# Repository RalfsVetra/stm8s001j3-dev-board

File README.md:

# STM8S001J3 development board

A simple and easy to use development board for STM8S001J3 microcontroller. This is a part of my larger project where I explore hardware and firmware.

## License
This project is licensed under the MIT License - see the [LICENSE](/LICENSE) file for details.

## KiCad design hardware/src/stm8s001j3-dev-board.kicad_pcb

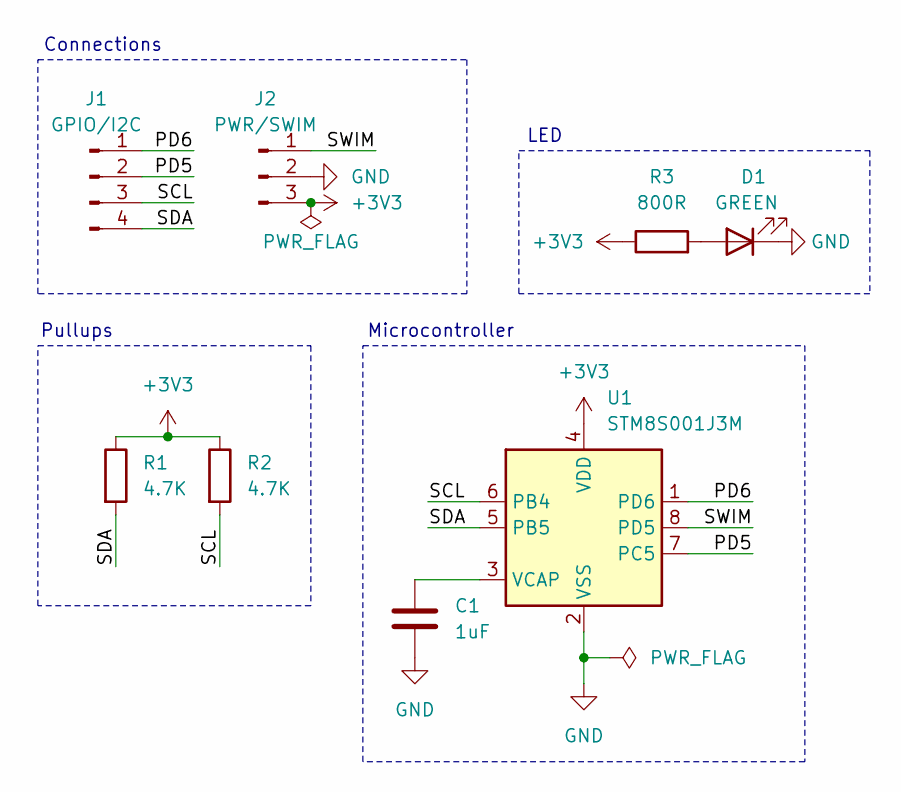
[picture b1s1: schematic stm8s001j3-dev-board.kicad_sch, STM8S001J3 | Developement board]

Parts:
C1: 1uF; C_0603_1608Metric
D1: GREEN; LED_0603_1608Metric
J1: GPIO/I2C; PinHeader_1x04_P2.54mm_Vertical
J2: PWR/SWIM; PinHeader_1x03_P2.54mm_Vertical
R1, R2: 4.7K; R_0603_1608Metric
R3: 800R; R_0603_1608Metric
U1: STM8S001J3M; SO-8_3.9x4.9mm_P1.27mm

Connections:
+3V3: J2.3, R1.1, R2.1, R3.1, U1.4 (VDD)
/PD5: J1.2, U1.7 (PC5)
/PD6: J1.1, U1.1 (PD6)
/SCL: J1.3, R2.2, U1.6 (PB4)
/SDA: J1.4, R1.2, U1.5 (PB5)
/SWIM: J2.1, U1.8 (PD5)
GND: C1.2, D1.1 (K), J2.2, U1.2 (VSS)
unnamed: D1.2 (A), R3.2
unnamed: C1.1, U1.3 (VCAP)

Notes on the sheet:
Connections
Microcontroller
Pullups
LED

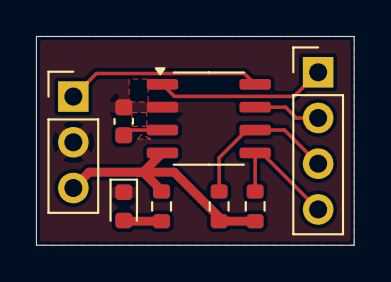
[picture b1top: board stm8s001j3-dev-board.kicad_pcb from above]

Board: 2 copper layers, 17.7 x 11.6 mm, 8 parts (0 on the bottom side), 9 nets.

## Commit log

2025-12-16 docs: add project introduction and license
2025-12-16 feat(hardware): add STM8S001J3 board design and fab files
    Introduce the STM8S001J3 development board design along with
    fabrication files.
    Include multiple compressed fabrication packages for fast PCB
    manufacturing uploads.
2025-12-16 fix: copyright licensing correction
